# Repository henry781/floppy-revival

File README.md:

# Floppy Revival

A Raspberry Pi Pico 2 board that connects a real 5.25" floppy drive to a
modern computer over USB. The computer sees an ordinary USB floppy drive:
insert a PC disk and it mounts, with no special software on the host side.

Supported media are the standard PC formats: 360 KB, 720 KB (96 tpi) and
1.2 MB, all MFM with 512-byte sectors. Reading, writing and formatting
work. The reference drive is a YE Data YD-380B (1.2 MB, 96 tpi).

## Disclaimer

This is a personal study project, published as is, in the hope that it is
useful or interesting to someone. It is not a product. There is no
warranty of any kind, and no support is promised.

Before you build one, be aware that:

- **It can destroy data.** A firmware bug, a wrong jumper or a wiring
  mistake can write over a disk. Never put a disk you cannot afford to
  lose in it without covering the write-protect notch.
- **It can damage the drive.** Swapped 12 V and 5 V wires, a reversed
  ribbon or a powered hot-plug will kill a 40-year-old drive that cannot
  be replaced.
- **The board has a switching power supply fed from a 19.5 V laptop
  adapter.** It was designed with care, simulated and measured, but it
  has been built and tested by one person, on one board, with one drive.
- **Rev C.1 itself has not been manufactured.** It is the tested rev C
  board plus a footprint for R33, a 470 ohm minimum-load resistor that was
  fitted by hand on the tested board. See [Status](#status).

Everything in this repository was checked as far as I could check it, and
the reasoning behind each choice is written down so that it can be
challenged. If you find a mistake, please open an issue.

## Status

| Part | State |
|---|---|
| Firmware | Working on the bench with macOS as the host: mounts, reads and writes 360 KB and 1.2 MB disks, handles disk swaps and ejects. Formatting (UFI FORMAT UNIT) is implemented and covered by host tests; the full bench test plan ([docs/testing.md](docs/testing.md)), including Windows and Linux, has not been completed. Codec, cache and USB layers have host-side unit tests. |
| Board rev C | Built and in use with a YD-380B. Needed one fix after the build: R33 across D5 (the unloaded 5 V rail crept up to 6.1 V without it). |
| Board rev C.1 | Rev C with a proper footprint for R33. ERC and DRC clean. Not yet manufactured. |
| USB identity | Uses TinyUSB's test VID/PID (0xCafe/0x5250). Fine on a bench, not for anything you hand out. See [docs/building.md](docs/building.md#usb-identity). |

Known problems are listed in [docs/testing.md](docs/testing.md#known-issues).

## How it works

```mermaid
flowchart LR
    host["Host computer"] -- USB --> pico
    pico["Pico 2 (RP2350)<br/>core 0: USB mass storage (UFI)<br/>core 1: drive control, flux capture, MFM"]
    pico -- "7407 buffers" --> ribbon["34-pin ribbon"] --> drive["5.25#quot; drive"]
    adapter["19.5 V adapter"] --> switch["Switch (Q1)"]
    pico -. "GP18" .-> switch
    switch --> bucks["LM2678 12 V<br/>LM2676 5 V"] --> molex["Molex power"] --> drive
```

**USB side.** The Pico enumerates as a USB mass storage device with the
UFI subclass, the one USB floppy drives use. The host's own floppy driver
does the rest: geometry, media changes, formatting. Requests from the host
are handed to the second core through a mailbox, and the USB stack keeps
running while the drive seeks and spins.

**Drive side.** The Pico drives the classic Shugart/PC interface through
two SN7407 open-collector buffers. A PIO state machine timestamps every
flux transition on the read line and DMA moves them to memory; a software
MFM decoder turns them into sectors as the track goes by. Writes go the
other way: sectors are MFM-encoded ahead of time and a second PIO program
plays the pulses out with the write gate opened at the right point of the
track. Only the sector being written is touched, as on a PC floppy
controller, and the track is read back afterwards to check it.

**Power.** Drives need 12 V and 5 V, more current than USB can give. The
board makes both from a laptop adapter with two buck regulators and LC
filters, and the firmware switches them on only once it is running and
sees a good adapter voltage. The drive is never powered while the Pico is
not, which matters because the Pico's inputs are only 5 V tolerant while
it is powered.

More detail:

- [docs/hardware.md](docs/hardware.md): circuit, design choices, bill of materials, power supply, smoke test and bring-up
- [docs/firmware.md](docs/firmware.md): firmware architecture and the reasons behind it
- [docs/pinmap.md](docs/pinmap.md): GPIO to drive pin mapping, drive jumpers and measurements
- [docs/assembly.md](docs/assembly.md): building the board
- [docs/building.md](docs/building.md): compiling and flashing the firmware, host tests
- [docs/user-guide.md](docs/user-guide.md): using it: LEDs, writing, changing, archiving and formatting disks
- [docs/testing.md](docs/testing.md): bench test plan and known issues
- [docs/references.md](docs/references.md): datasheets, specifications and related projects

## Repository layout

```
firmware/            Pico SDK project (C, PIO), host tests, tools
hardware/kicad/      KiCad 10 project: schematic, PCB, project library
hardware/fabrication/  Gerbers, drill file, BOM exported from the project
hardware/simulation/ ngspice decks used to size the power supply
hardware/floppy-revival-schematic.pdf
docs/                documentation
```

## Quick start

1. Read the disclaimer above and [docs/hardware.md](docs/hardware.md).
2. Order the PCB from `hardware/fabrication/gerbers/` (2 layers, 1.6 mm,
   1 oz) and the parts from the BOM in `docs/hardware.md`.
3. Build the firmware ([docs/building.md](docs/building.md)) or flash a
   release UF2 if one is attached to the GitHub release.
4. Assemble and test in the order of [docs/assembly.md](docs/assembly.md).
   The power supply is checked with nothing connected to it, and the board
   is checked without the drive, before the drive is ever connected.

## Credits

The floppy back end started as a port of
[pico-mfm-floppy](https://github.com/jackdoe/pico-mfm-floppy) by jackdoe
(MIT), which showed that DMA-fed PIO flux capture on a Pico is enough to
read MFM in real time. [Adafruit_Floppy](https://github.com/adafruit/Adafruit_Floppy)
was the reference for format detection and the USB mass storage approach.
USB runs on [TinyUSB](https://github.com/hathach/tinyusb) through the
[Raspberry Pi Pico SDK](https://github.com/raspberrypi/pico-sdk). Details
and licences in [THIRD_PARTY.md](THIRD_PARTY.md).

## Licence

- Firmware: MIT
- Hardware (KiCad files, fabrication outputs, simulations): CERN-OHL-P-2.0
- Documentation: CC-BY-4.0

See [LICENSE](LICENSE) and the `LICENSES/` folder. Third-party files keep
their own licences, listed in [THIRD_PARTY.md](THIRD_PARTY.md).

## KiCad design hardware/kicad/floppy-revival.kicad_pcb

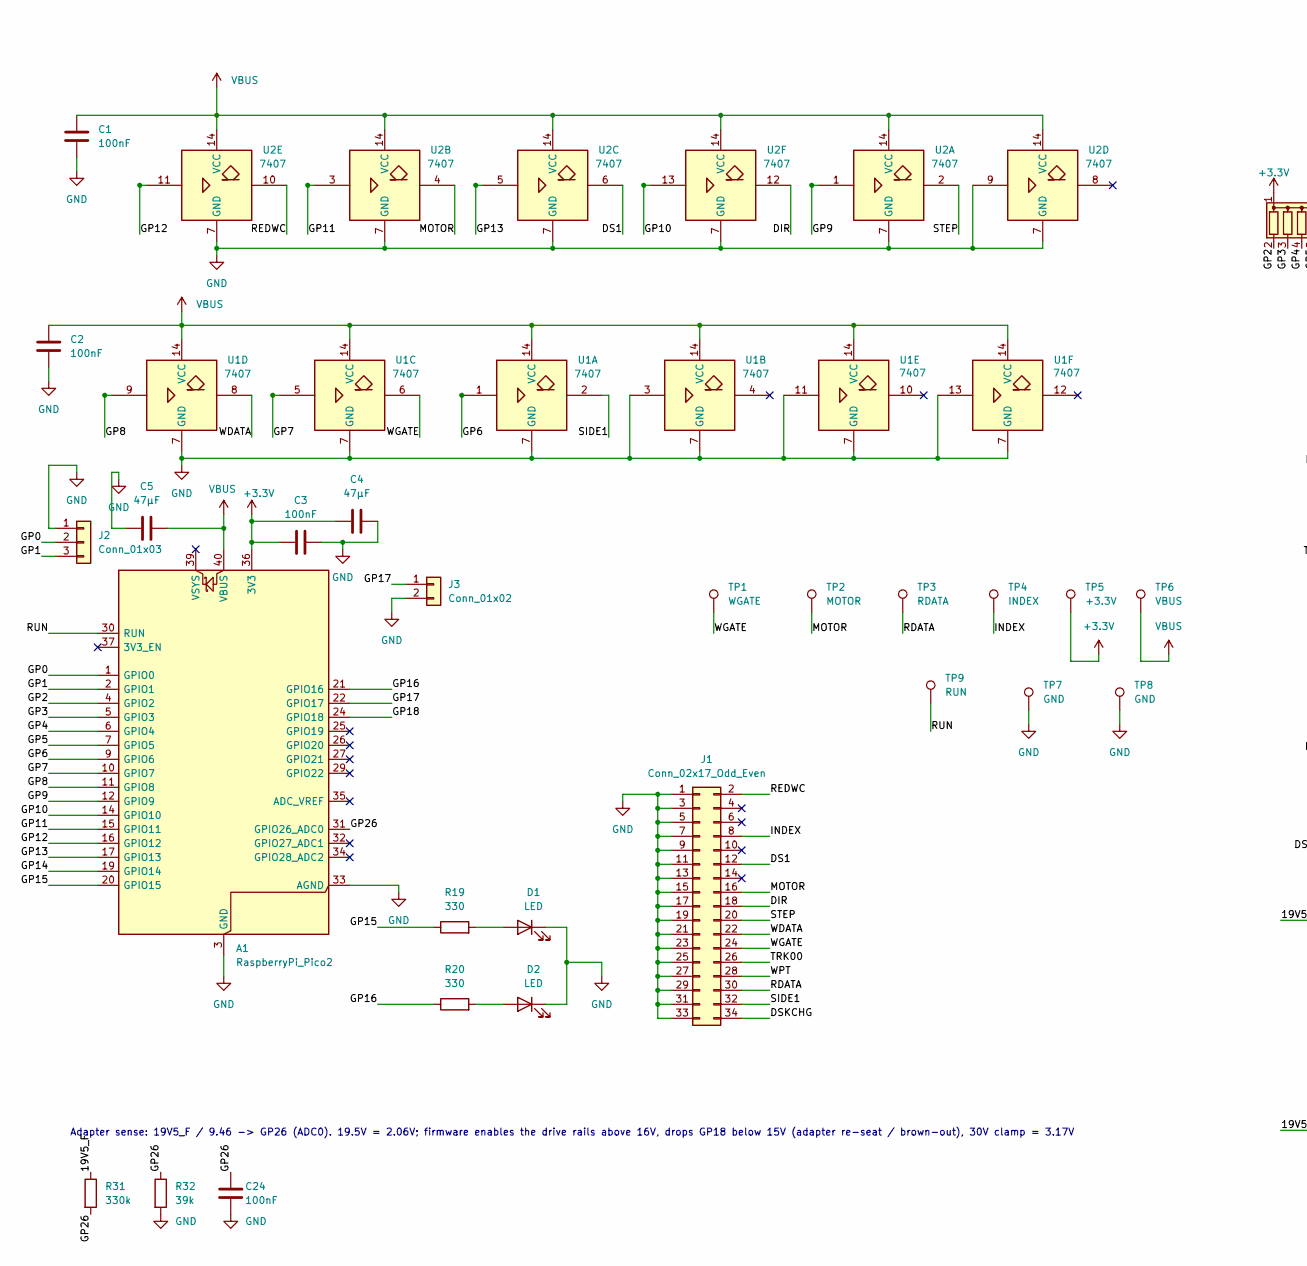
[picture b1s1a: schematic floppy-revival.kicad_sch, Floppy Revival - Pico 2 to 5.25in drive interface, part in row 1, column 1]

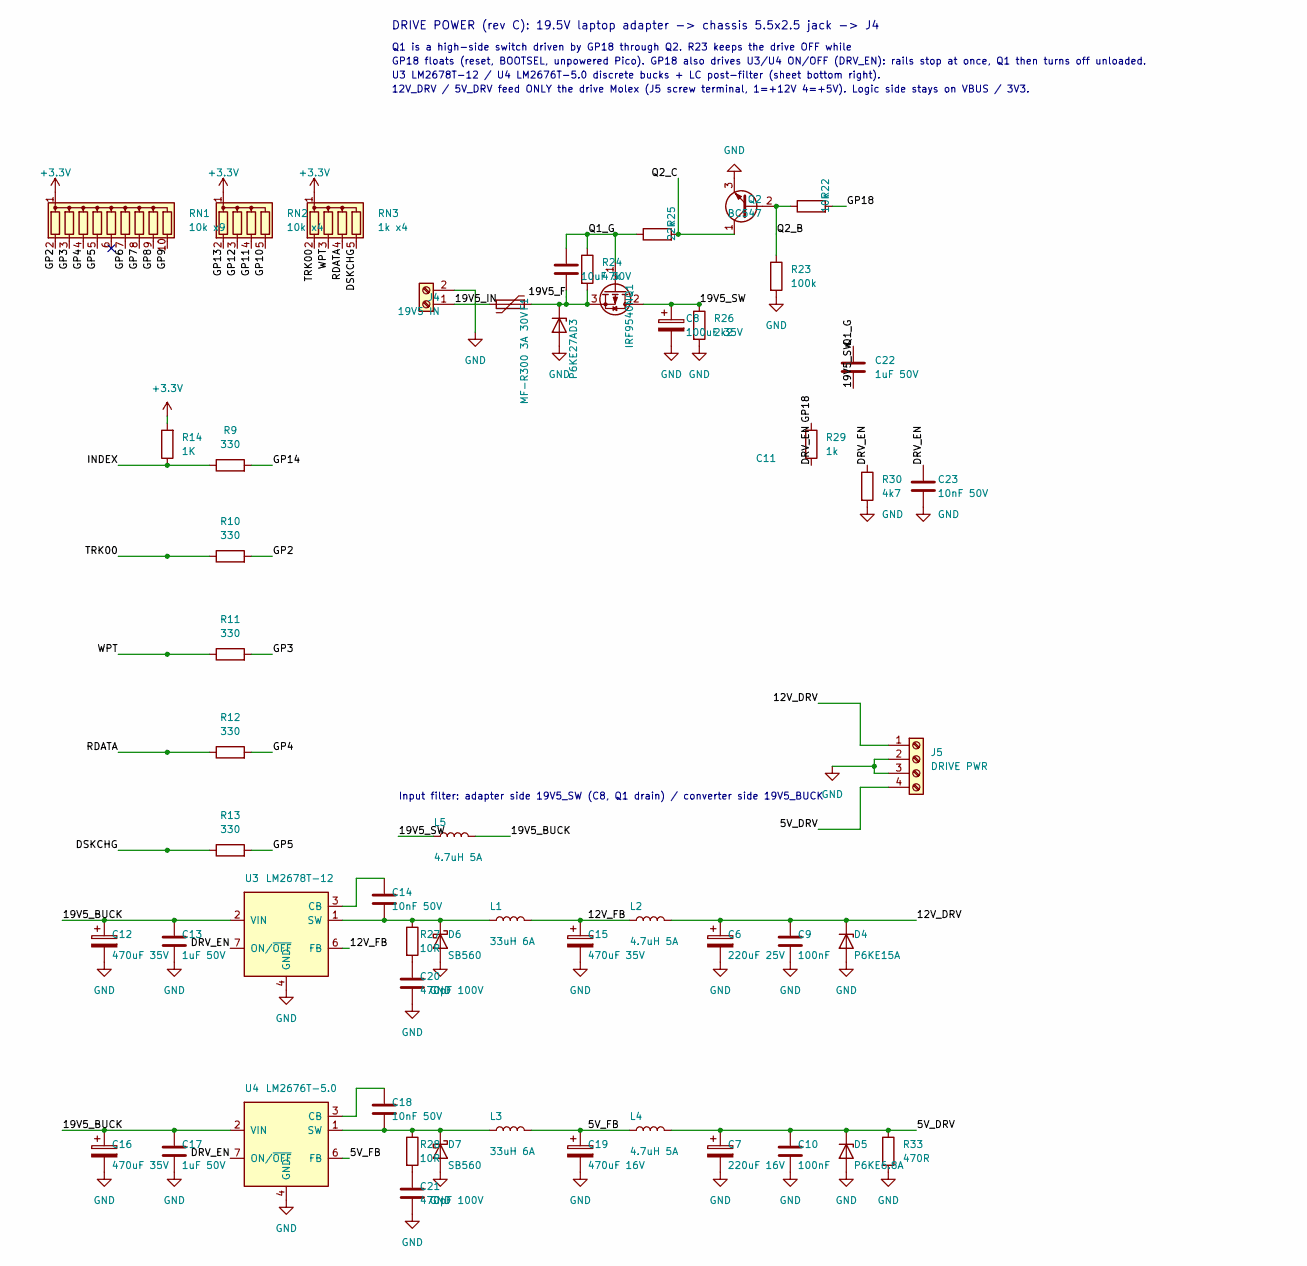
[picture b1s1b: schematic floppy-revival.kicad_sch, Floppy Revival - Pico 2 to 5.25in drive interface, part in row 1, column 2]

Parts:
A1: RaspberryPi_Pico2; RaspberryPi_Pico_Common_SMD
C1, C2, C3: 100nF; C_Disc_D3.0mm_W1.6mm_P2.50mm
C4, C5: 47µF; CP_Radial_D5.0mm_P2.00mm
C6: 220uF 25V; CP_Radial_D8.0mm_P3.50mm
C7: 220uF 16V; CP_Radial_D6.3mm_P2.50mm
C8: 100uF 35V; CP_Radial_D8.0mm_P3.50mm
C9, C10, C24: 100nF; C_Disc_D5.1mm_W3.2mm_P5.00mm
C11: 10uF 50V; C_Disc_D6.0mm_W4.4mm_P5.00mm
C12, C15, C16: 470uF 35V; CP_Radial_D8.0mm_P3.50mm
C13, C17, C22: 1uF 50V; C_Disc_D5.1mm_W3.2mm_P5.00mm
C14, C18, C23: 10nF 50V; C_Disc_D5.1mm_W3.2mm_P5.00mm
C19: 470uF 16V; CP_Radial_D8.0mm_P3.50mm
C20, C21: 470pF 100V; C_Disc_D5.1mm_W3.2mm_P5.00mm
D1, D2: LED; LED_D3.0mm_Horizontal_O6.35mm_Z6.0mm
D3: P6KE27A; D_DO-15_P10.16mm_Horizontal
D4: P6KE15A; D_DO-15_P10.16mm_Horizontal
D5: P6KE6.8A; D_DO-15_P10.16mm_Horizontal
D6, D7: SB560; D_DO-201AD_P5.08mm_Vertical_AnodeUp
F1: MF-R300 3A 30V; PTC_Radial_P5.08mm
J1: Conn_02x17_Odd_Even; IDC-Header_2x17_P2.54mm_Vertical
J2: Conn_01x03; PinHeader_1x03_P2.54mm_Vertical
J3: Conn_01x02; PinHeader_1x02_P2.54mm_Vertical
J4: 19V5 IN; TerminalBlock_Phoenix_MKDS-1,5-2-5.08_1x02_P5.08mm_Horizont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
J5: DRIVE PWR; TerminalBlock_Phoenix_MKDS-1,5-4-5.08_1x04_P5.08mm_Horizont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
L1, L3: 33uH 6A; L_Toroid_Vertical_D22.0mm_W11.0mm_P9.00mm
L2, L4, L5: 4.7uH 5A; L_Radial_D7.5mm_P3.00mm
Q1: IRF9540N; TO-220-3_Vertical
Q2: BC547; TO-92_Inline_Wide
R9, R10, R11, R12, R13, R19, R20: 330; R_Axial_DIN0207_L6.3mm_D2.5mm_P10.16mm_Horizontal
R14: 1K; R_Axial_DIN0207_L6.3mm_D2.5mm_P10.16mm_Horizontal
R22: 10k; R_Axial_DIN0207_L6.3mm_D2.5mm_P10.16mm_Horizontal
R23: 100k; R_Axial_DIN0207_L6.3mm_D2.5mm_P10.16mm_Horizontal
R24: 47k; R_Axial_DIN0207_L6.3mm_D2.5mm_P10.16mm_Horizontal
R25: 22k; R_Axial_DIN0207_L6.3mm_D2.5mm_P10.16mm_Horizontal
R26: 2k2; R_Axial_DIN0207_L6.3mm_D2.5mm_P10.16mm_Horizontal
R27, R28: 10R; R_Axial_DIN0207_L6.3mm_D2.5mm_P10.16mm_Horizontal
R29: 1k; R_Axial_DIN0207_L6.3mm_D2.5mm_P10.16mm_Horizontal
R30: 4k7; R_Axial_DIN0207_L6.3mm_D2.5mm_P10.16mm_Horizontal
R31: 330k; R_Axial_DIN0207_L6.3mm_D2.5mm_P7.62mm_Horizontal
R32: 39k; R_Axial_DIN0207_L6.3mm_D2.5mm_P7.62mm_Horizontal
R33: 470R; R_Axial_DIN0207_L6.3mm_D2.5mm_P10.16mm_Horizontal
RN1: 10k x9; R_Array_SIP10
RN2: 10k x4; R_Array_SIP5
RN3: 1k x4; R_Array_SIP5
TP1: WGATE; TestPoint_THTPad_D2.0mm_Drill1.0mm
TP2: MOTOR; TestPoint_THTPad_D2.0mm_Drill1.0mm
TP3: RDATA; TestPoint_THTPad_D2.0mm_Drill1.0mm
TP4: INDEX; TestPoint_THTPad_D2.0mm_Drill1.0mm
TP5: +3.3V; TestPoint_THTPad_D2.0mm_Drill1.0mm
TP6: VBUS; TestPoint_THTPad_D2.0mm_Drill1.0mm
TP7, TP8: GND; TestPoint_THTPad_D2.0mm_Drill1.0mm
TP9: RUN; TestPoint_THTPad_D2.0mm_Drill1.0mm
U1, U2: 7407; DIP-14_W7.62mm
U3: LM2678T-12; TO-220-7_P2.54x5.08mm_StaggerOdd_Lead3.08mm_Vertical
U4: LM2676T-5.0; TO-220-7_P2.54x5.08mm_StaggerOdd_Lead3.08mm_Vertical

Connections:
+3.3V: A1.36 (3V3), C3.2, C4.1, R14.2, RN1.1 (common), RN2.1 (common), RN3.1 (common), TP5.1 (1_1)
/5V_DRV: C7.1, C10.1, D5.1 (K), J5.4, L4.2, R33.1
/5V_FB: C19.1, L3.2, L4.1, U4.6 (FB)
/12V_DRV: C6.1, C9.1, D4.1 (K), J5.1, L2.2
/12V_FB: C15.1, L1.2, L2.1, U3.6 (FB)
/19V5_BUCK: C12.1, C13.1, C16.1, C17.1, L5.2, U3.2 (VIN), U4.2 (VIN)
/19V5_F: C11.2, D3.1 (K), F1.1, Q1.3 (S), R24.2, R31.1
/19V5_IN: F1.2, J4.1
/19V5_SW: C8.1, C22.2, L5.1, Q1.2 (D), R26.1
/DIR: J1.18, U2.12
/DRV_EN: C23.1, R29.2, R30.1, U3.7 (ON/~OFF), U4.7 (ON/~OFF)
/DS1: J1.12, U2.6
/DSKCHG: J1.34, R13.1, RN3.5 (R4)
/GP0: A1.1 (GPIO0), J2.2
/GP1: A1.2 (GPIO1), J2.3
/GP2: A1.4 (GPIO2), R10.2, RN1.2 (R1)
/GP3: A1.5 (GPIO3), R11.2, RN1.3 (R2)
/GP4: A1.6 (GPIO4), R12.2, RN1.4 (R3)
/GP5: A1.7 (GPIO5), R13.2, RN1.5 (R4)
/GP6: A1.9 (GPIO6), RN1.7 (R6), U1.1
/GP7: A1.10 (GPIO7), RN1.8 (R7), U1.5
/GP8: A1.11 (GPIO8), RN1.9 (R8), U1.9
/GP9: A1.12 (GPIO9), RN1.10 (R9), U2.1
/GP10: A1.14 (GPIO10), RN2.5 (R4), U2.13
/GP11: A1.15 (GPIO11), RN2.4 (R3), U2.3
/GP12: A1.16 (GPIO12), RN2.3 (R2), U2.11
/GP13: A1.17 (GPIO13), RN2.2 (R1), U2.5
/GP14: A1.19 (GPIO14), R9.2
/GP15: A1.20 (GPIO15), R19.1
/GP16: A1.21 (GPIO16), R20.1
/GP17: A1.22 (GPIO17), J3.1
/GP18: A1.24 (GPIO18), R22.2, R29.1
/GP26: A1.31 (GPIO26_ADC0), C24.1, R31.2, R32.1
/INDEX: J1.8, R9.1, R14.1, TP4.1 (1_1)
/MOTOR: J1.16, TP2.1 (1_1), U2.4
/Q1_G: C11.1, C22.1, Q1.1 (G), R24.1, R25.1
/Q2_B: Q2.2 (B), R22.1, R23.1
/Q2_C: Q2.1 (C), R25.2
/RDATA: J1.30, R12.1, RN3.4 (R3), TP3.1 (1_1)
/REDWC: J1.2, U2.10
/RUN: A1.30 (RUN), TP9.1 (1_1)
/SIDE1: J1.32, U1.2
/STEP: J1.20, U2.2
/TRK00: J1.26, R10.1, RN3.2 (R1)
/WDATA: J1.22, U1.8
/WGATE: J1.24, TP1.1 (1_1), U1.6
/WPT: J1.28, R11.1, RN3.3 (R2)
GND: A1.3 (GND), A1.8 (GND), A1.13 (GND), A1.18 (GND), A1.23 (GND), A1.28 (GND), A1.33 (AGND), A1.38 (GND), C1.2, C2.2, C3.1, C4.2, C5.2, C6.2, C7.2, C8.2, C9.2, C10.2, C12.2, C13.2, C15.2, C16.2, C17.2, C19.2, C20.2, C21.2, C23.2, C24.2, D1.1 (K), D2.1 (K), D3.2 (A), D4.2 (A), D5.2 (A), D6.2 (A), D7.2 (A), J1.1, J1.3, J1.5, J1.7, J1.9, J1.11, J1.13, J1.15, J1.17, J1.19, J1.21, J1.23, J1.25, J1.27, J1.29, J1.31, J1.33, J2.1, J3.2, J4.2, J5.2, J5.3, Q2.3 (E), R23.2, R26.2, R30.2, R32.2, R33.2, TP7.1 (1_1), TP8.1 (1_1), U1.3, U1.7 (GND), U1.11, U1.13, U2.7 (GND), U2.9, U3.4 (GND), U4.4 (GND)
unnamed: C20.1, R27.2
unnamed: C21.1, R28.2
unnamed: D1.2 (A), R19.2
unnamed: D2.2 (A), R20.2
unnamed: C14.2, D6.1 (K), L1.1, R27.1, U3.1 (SW)
unnamed: C18.2, D7.1 (K), L3.1, R28.1, U4.1 (SW)
unnamed: C14.1, U3.3 (CB)
unnamed: C18.1, U4.3 (CB)
VBUS: A1.40 (VBUS), C1.1, C2.1, C5.1, TP6.1 (1_1), U1.14 (VCC), U2.14 (VCC)

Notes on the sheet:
DRIVE POWER (rev C): 19.5V laptop adapter -> chassis 5.5x2.5 jack -> J4
Q1 is a high-side switch driven by GP18 through Q2. R23 keeps the drive OFF while
GP18 floats (reset, BOOTSEL, unpowered Pico). GP18 also drives U3/U4 ON/OFF (DRV_EN): rails stop at once, Q1 then turns off unloaded.
U3 LM2678T-12 / U4 LM2676T-5.0 discrete bucks + LC post-filter (sheet bottom right).
12V_DRV / 5V_DRV feed ONLY the drive Molex (J5 screw terminal, 1=+12V 4=+5V). Logic side stays on VBUS / 3V3.
Input filter: adapter side 19V5_SW (C8, Q1 drain) / converter side 19V5_BUCK
Adapter sense: 19V5_F / 9.46 -> GP26 (ADC0). 19.5V = 2.06V; firmware enables the drive rails above 16V, drops GP18 below 15V (adapter re-seat / brown-out), 30V clamp = 3.17V

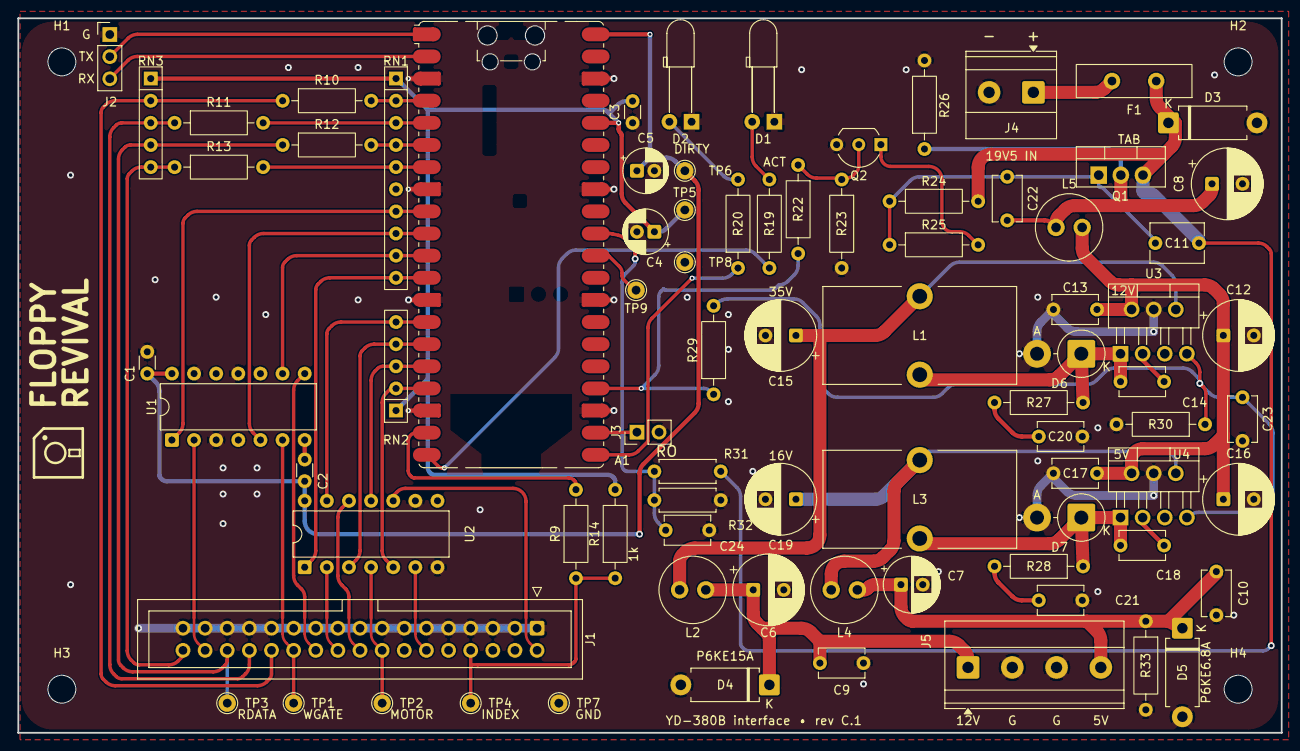
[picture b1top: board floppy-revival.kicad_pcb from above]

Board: 2 copper layers, 145.0 x 82.0 mm, 85 parts (0 on the bottom side), 57 nets.

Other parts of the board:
H1, H2, H3, H4: MountingHole_3.2mm_M3

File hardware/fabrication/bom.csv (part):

"Reference","Value","QUANTITY","Description","Footprint"
"A1","RaspberryPi_Pico2","1","Raspberry Pi Pico 2 (RP2350), soldered flat by its castellations","Module:RaspberryPi_Pico_Common_SMD"
"C1","100nF","1","100nF X7R ceramic, 2.5 mm, Murata RCER71H104K0DBH03A; at U1 VCC (pin 14)","Capacitor_THT:C_Disc_D3.0mm_W1.6mm_P2.50mm"
"C2","100nF","1","100nF X7R ceramic, 2.5 mm, Murata RCER71H104K0DBH03A; at U2 VCC (pin 14)","Capacitor_THT:C_Disc_D3.0mm_W1.6mm_P2.50mm"
"C3","100nF","1","100nF X7R ceramic, 2.5 mm, Murata RCER71H104K0DBH03A; at the Pico 3V3(OUT)","Capacitor_THT:C_Disc_D3.0mm_W1.6mm_P2.50mm"
"C4","47µF","1","47uF 25V electrolytic, Panasonic FR EEUFR1E470 (D5x11, P2.0); 3.3V rail (polarized: pad 1 = +)","Capacitor_THT:CP_Radial_D5.0mm_P2.00mm"
"C5","47µF","1","47uF 25V electrolytic, Panasonic FR EEUFR1E470 (D5x11, P2.0); VBUS at the Pico (polarized: pad 1 = +), total VBUS capacitance kept under ~100uF","Capacitor_THT:CP_Radial_D5.0mm_P2.00mm"
"C6","220uF 25V","1","post-filter cap, Panasonic FR EEUFR1E221 (D8x11.5, 3.5mm), at the drive terminal","Capacitor_THT:CP_Radial_D8.0mm_P3.50mm"
"C7","220uF 16V","1","post-filter cap, Panasonic FR EEUFR1C221 (D6.3x11.2, 2.5mm), at the drive terminal","Capacitor_THT:CP_Radial_D6.3mm_P2.50mm"
"C8","100uF 35V","1","100uF 35V low-ESR 105C electrolytic, Panasonic FC EEUFC1V101 (D8x11.5, P3.5); switched-node bulk, first cap of the input pi filter","Capacitor_THT:CP_Radial_D8.0mm_P3.50mm"
"C9,C10","100nF","2","rail HF decoupling at J5; Murata RDER71H104K0K1H03B (5 mm pitch)","Capacitor_THT:C_Disc_D5.1mm_W3.2mm_P5.00mm"
"C11","10uF 50V","1","Q1 gate-source, TDK FG20X7R1H106KRT06 (10uF 50V X7R, 5 mm): ~10 x C22 so an adapter hot-plug cannot couple Q1 on through C22","Capacitor_THT:C_Disc_D6.0mm_W4.4mm_P5.00mm"
"C12,C16","470uF 35V","2","buck input bulk, Panasonic FR EEUFR1V471L (D8x20, 3.5mm, 1.56A ripple), right at VIN/GND","Capacitor_THT:CP_Radial_D8.0mm_P3.50mm"
"C13,C17","1uF 50V","2","X7R high-frequency input bypass, closest to VIN pin 2; Murata RDER71H105K2K1H03B","Capacitor_THT:C_Disc_D5.1mm_W3.2mm_P5.00mm"
"C14,C18","10nF 50V","2","bootstrap capacitor CB-SW (datasheet: 0.01 uF); Murata RDER71H103K0K1H03B (5 mm pitch)","Capacitor_THT:C_Disc_D5.1mm_W3.2mm_P5.00mm"
"C15","470uF 35V","1","buck output cap, Panasonic FR EEUFR1V471L (D8x20, 3.5mm, 30mOhm, same part as the input caps); ESR sets loop stability (datasheet 7.1.3)","Capacitor_THT:CP_Radial_D8.0mm_P3.50mm"
"C19","470uF 16V","1","buck output cap, Panasonic FR EEUFR1C471 (D8x11.5, 3.5mm, 56mOhm); ESR sets loop stability (datasheet 7.1.3)","Capacitor_THT:CP_Radial_D8.0mm_P3.50mm"
"C20","470pF 100V","1","SW snubber capacitor 470pF 100V C0G, Murata RDE5C2A471J0M1H03A (5 mm pitch), REQUIRED (with R27)","Capacitor_THT:C_Disc_D5.1mm_W3.2mm_P5.00mm"
"C21","470pF 100V","1","SW snubber capacitor 470pF 100V C0G, Murata RDE5C2A471J0M1H03A (5 mm pitch), REQUIRED (with R28)","Capacitor_THT:C_Disc_D5.1mm_W3.2mm_P5.00mm"
"C22","1uF 50V","1","Q1 Miller capacitor gate-drain, Murata RDER71H105K2K1H03B (1uF 50V X7R, 5 mm): dV/dt ~1 V/ms, adapter peak ~1.9A into the ~1 mF behind Q1 (simulated)","Capacitor_THT:C_Disc_D5.1mm_W3.2mm_P5.00mm"
"C23","10nF 50V","1","DRV_EN filter at the ON/OFF pins, Murata RDER71H103K0K1H03B (5 mm pitch)","Capacitor_THT:C_Disc_D5.1mm_W3.2mm_P5.00mm"
"C24","100nF","1","adapter sense filter at GP26 (tau 3.5 ms with R31||R32); Murata RDER71H104K0K1H03B (5 mm pitch)","Capacitor_THT:C_Disc_D5.1mm_W3.2mm_P5.00mm"
"D1","LED","1","LED 3 mm green (ACT), horizontal mount","LED_THT:LED_D3.0mm_Horizontal_O6.35mm_Z6.0mm"
"D2","LED","1","LED 3 mm red (DIRTY), horizontal mount","LED_THT:LED_D3.0mm_Horizontal_O6.35mm_Z6.0mm"
"D3","P6KE27A","1","TVS Littelfuse P6KE27A (standoff 23.1V: margin for 20V adapters), input surge clamp","Diode_THT:D_DO-15_P10.16mm_Horizontal"
"D4","P6KE15A","1","12V rail TVS, Littelfuse P6KE15A: a shorted regulator switch would put 19.5V on the drive","Diode_THT:D_DO-15_P10.16mm_Horizontal"
"D5","P6KE6.8A","1","5V rail TVS, Littelfuse P6KE6.8A: a shorted regulator switch would put 19.5V on the drive logic","Diode_THT:D_DO-15_P10.16mm_Horizontal"
"D6,D7","SB560","2","catch diode, Vishay SB560-E3/54 (60V 5A Schottky): simulated reverse peak <= 35V with the snubber","Diode_THT:D_DO-201AD_P5.08mm_Vertical_AnodeUp"
"F1","MF-R300 3A 30V","1","Resettable PTC fuse, 3A hold / 6A trip, 30V max (MF-RG is only 16V!)","FloppyRevival:PTC_Radial_P5.08mm"
"J1","Conn_02x17_Odd_Even","1","34-pin (2x17) box header, 2.54 mm, vertical, keyed","Connector_IDC:IDC-Header_2x17_P2.54mm_Vertical"
"J2","Conn_01x03","1","1x3 pin header 2.54 mm (UART: GND, TX, RX)","Connector_PinHeader_2.54mm:PinHeader_1x03_P2.54mm_Vertical"
"J3","Conn_01x02","1","1x2 pin header 2.54 mm + jumper (read-only)","Connector_PinHeader_2.54mm:PinHeader_1x02_P2.54mm_Vertical"
"J4","19V5 IN","1","Phoenix Contact MKDS 1,5/2-5,08 (1715721), 19.5V DC input (pin 1 = +, pin 2 = GND)","TerminalBlock_Phoenix:TerminalBlock_Phoenix_MKDS-1,5-2-5.08_1x02_P5.08mm_Horizontal"
"J5","DRIVE PWR","1","Phoenix Contact MKDS 1,5/4-5,08 (1715747) to the drive Molex: 1=+12V 2=GND 3=GND 4=+5V","TerminalBlock_Phoenix:TerminalBlock_Phoenix_MKDS-1,5-4-5.08_1x04_P5.08mm_Horizontal"
"L1,L3","33uH 6A","2","buck inductor, Feryster DTMSS-16/0.033/6.0-V sendust toroid (33uH at 0A, 23uH at 6A, 24.5mOhm)","FloppyRevival:L_Toroid_Vertical_D22.0mm_W11.0mm_P9.00mm"
"L2,L4","4.7uH 5A","2","post-filter inductor, Ferrocore COIL0608-0.0047 (4.7uH, Isat 5A, 22.9mOhm)","FloppyRevival:L_Radial_D7.5mm_P3.00mm"
"L5","4.7uH 5A","1","input filter inductor, Ferrocore COIL0608-0.0047: with C8 and the bulk caps a pi filter keeping the 260 kHz input current off the adapter cable (Z0 ~0.07 ohm << converter input ~16 ohm, no Middlebrook issue)","FloppyRevival:L_Radial_D7.5mm_P3.00mm"
"Q1","IRF9540N","1","P-MOSFET high-side switch, Infineon IRF9540NPBF (-100V, 23A, TO-220 G-D-S)","Package_TO_SOT_THT:TO-220-3_Vertical"
"Q2","BC547","1","NPN level shifter GP18 -> Q1 gate, BC547B (TO-92 C-B-E, outer legs bent to 2.54 mm)","Package_TO_SOT_THT:TO-92_Inline_Wide"
"R9-R13,R19,R20","330","7","metal film 0.25W 1%, axial","Resistor_THT:R_Axial_DIN0207_L6.3mm_D2.5mm_P10.16mm_Horizontal"
"R14","1K","1","metal film 0.25W 1%, axial","Resistor_THT:R_Axial_DIN0207_L6.3mm_D2.5mm_P10.16mm_Horizontal"
"R22","10k","1","Q2 base series resistor; metal film 0.25W 1%, axial","Resistor_THT:R_Axial_DIN0207_L6.3mm_D2.5mm_P10.16mm_Horizontal"
"R23","100k","1","Q2 base pull-down: drive power stays OFF while GP18 floats (reset/boot/BOOTSEL); metal film 0.25W 1%, axial","Resistor_THT:R_Axial_DIN0207_L6.3mm_D2.5mm_P10.16mm_Horizontal"
"R24","47k","1","Q1 gate-source pull-up (switch OFF by default); metal film 0.25W 1%, axial","Resistor_THT:R_Axial_DIN0207_L6.3mm_D2.5mm_P10.16mm_Horizontal"
"R25","22k","1","Q1 gate divider: Vgs = -19.5V x 47/(47+22) = -13V (|Vgs| < 20V max); metal film 0.25W 1%, axial","Resistor_THT:R_Axial_DIN0207_L6.3mm_D2.5mm_P10.16mm_Horizontal"
"R26","2k2","1","Bleed on the switched 19.5V node, Vishay MRS25 2k2 0.6W (173 mW): the ~1 mF behind Q1 is below the regulators' 7.9V lockout 2.6 s after GP18 drops (simulated), inside the firmware's 3.5 s hold","Resistor_THT:R_Axial_DIN0207_L6.3mm_D2.5mm_P10.16mm_Horizontal"
"R27,R28","10R","2","SW snubber resistor 10R 1/4W (~25 mW), REQUIRED: without it the catch diode sees up to 40V (simulated)","Resistor_THT:R_Axial_DIN0207_L6.3mm_D2.5mm_P10.16mm_Horizontal"
"R29","1k","1","GP18 -> regulator ON/OFF pins (DRV_EN); metal film 0.25W 1%, axial","Resistor_THT:R_Axial_DIN0207_L6.3mm_D2.5mm_P10.16mm_Horizontal"
"R30","4k7","1","DRV_EN pull-down: < 0.43V against the 2 x 45uA ON/OFF pull-ups while GP18 floats; metal film 0.25W 1%, axial","Resistor_THT:R_Axial_DIN0207_L6.3mm_D2.5mm_P10.16mm_Horizontal"
"R31","330k","1","adapter sense divider top, 19V5_F -> GP26; metal film 0.25W 1%, axial (57 uA into an unpowered Pico pad)","Resistor_THT:R_Axial_DIN0207_L6.3mm_D2.5mm_P7.62mm_Horizontal"
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
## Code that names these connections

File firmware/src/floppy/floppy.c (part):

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// /WGATE goes false; the retry paths re-seek right after a write.
#define FLOPPY_WGATE_HOLD_US 1000u

// Idle DSKCHG sample: how long /DRVSB is pulsed before pin 34 is read.
// Long enough for the drive's output gating and the 1k pull-up, far too
// short to light the drive's front LED.
#ifndef FLOPPY_DSKCHG_SAMPLE_US
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      if (values[i] == values[j]) return false;
    }
  }
  return pins->index < 32u && pins->read_data < 32u && pins->write_data < 32u;
}

static void floppy_pin_oc(uint pin, bool high) {
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                                            uint32_t timeout,
                                            uint32_t generation) {
  uint32_t start = now_ms();
  while (!gpio_get(f->pins.index)) {
    floppy_update_media(f);
    if (f->media_generation != generation) return DISK_ERR_MEDIA_CHANGED;
    if (elapsed(start, timeout) || deadline_elapsed(deadline)) return DISK_ERR_TIMEOUT;
    tight_loop_contents();
  }
  while (gpio_get(f->pins.index)) {
    floppy_update_media(f);
    if (f->media_generation != generation) return DISK_ERR_MEDIA_CHANGED;
    if (elapsed(start, timeout) || deadline_elapsed(deadline)) return DISK_ERR_TIMEOUT;
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
static void floppy_motor_line_on(floppy_t *f) {
  if (!f->motor_on) {
    FTRACE("motor ON (pin 16 low)\n");
    floppy_pin_oc(f->pins.motor_enable, false);
    f->motor_on = true;
    f->motor_qualified = false;
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  floppy_touch(f);
  disk_err_t status = floppy_select_internal(f, true, deadline);
  if (status != DISK_OK) return status;
  // Latch first: a step while selected clears DSKCHG with the spindle
  // stopped, so probing an empty drive never spins the motor.
  status = floppy_clear_media_latch(f, deadline, expected_generation);
  if (status != DISK_OK) return status;
  floppy_motor_line_on(f);
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                                           uint32_t generation) {
  floppy_update_media(f);
  if (!f->disk_change_active) {
    FTRACE("DSKCHG (pin 34) inactive\n");
    return DISK_OK;
  }
  // Any step pulse while selected clears the latch when a disk is in. At
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  // swap mid-operation) costs one seek out first.
  disk_err_t status;
  if (!floppy_at_track0(f)) {
    FTRACE("DSKCHG (pin 34) ACTIVE: head not at TRK00, seeking out first\n");
    bool moved = false;
    status = floppy_seek_track0_internal(f, deadline, generation, &moved);
    if (status != DISK_OK) return status;
  }
  FTRACE("DSKCHG (pin 34) ACTIVE: step pulse out at TRK00 (head stays put)\n");
  status = floppy_step_internal(f, DIR_OUTWARD, deadline, generation);
  if (status != DISK_OK) return status;
  sleep_ms(FLOPPY_HEAD_SETTLE_MS);
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  f->track0_confirmed = false;
  for (unsigned step = 0; step < FLOPPY_SEEK_HOME_STEPS_MAX; step++) {
    if (floppy_at_track0(f)) {
      FTRACE("TRK00 (pin 26) seen after %u step(s) out\n", step);
      f->cylinder = 0;
      f->track0_confirmed = true;
      return DISK_OK;
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    if (status != DISK_OK) return status;
    *moved = true;
  }
  FTRACE("TRK00 (pin 26) never seen after %u steps out\n", FLOPPY_SEEK_HOME_STEPS_MAX);
  return DISK_ERR_NO_TRACK0;
}

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                                      const floppy_deadline_t *deadline) {
  disk_err_t status = floppy_read_flux(f, expected_generation, goal, deadline);
  if (status == DISK_OK || !floppy_status_retryable(status)) return status;
  // No index pulses at all means the spindle never ran (drive unpowered,
  // no disk): stepping around cannot help and would count as a TRK00
  // fault, so give the plain timeout back.
  if (status == DISK_ERR_TIMEOUT && !f->motor_qualified) return status;
  // Probing a format whose data rate shows no MFM: the next candidate is
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    return flux_tx_fail(tx, DISK_ERR_TIMEOUT);
  }
  if (!tx->started) return true;
  bool index = gpio_get(f->pins.index);
  if (index) tx->index_armed = true;
  if (!tx->index_armed || index) return true;
  uint32_t fed = flux_tx_fed(tx);
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}

static void floppy_release(floppy_t *f) {
  if (f->gpio_configured) floppy_stop(f); // /WGATE released first
  if (f->read_sm_claimed) pio_sm_set_enabled(f->read.pio, f->read.sm, false);
  if (f->write_sm_claimed) {
    pio_sm_set_enabled(f->write.pio, f->write.sm, false);
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  }
  f->dma_tx_claimed = true;

  uint inputs[] = {f->pins.index, f->pins.track0, f->pins.write_protect,
                   f->pins.read_data, f->pins.disk_change};
  for (size_t i = 0; i < sizeof(inputs) / sizeof(inputs[0]); i++) {
    gpio_init(inputs[i]);
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  floppy_apply_density(f);

  if (flux_read_program_init(f->read.pio, f->read.sm, f->read.offset,
                             f->pins.read_data, f->pins.index) != 0) {
    floppy_release(f);
    return DISK_ERR_IO;
  }
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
